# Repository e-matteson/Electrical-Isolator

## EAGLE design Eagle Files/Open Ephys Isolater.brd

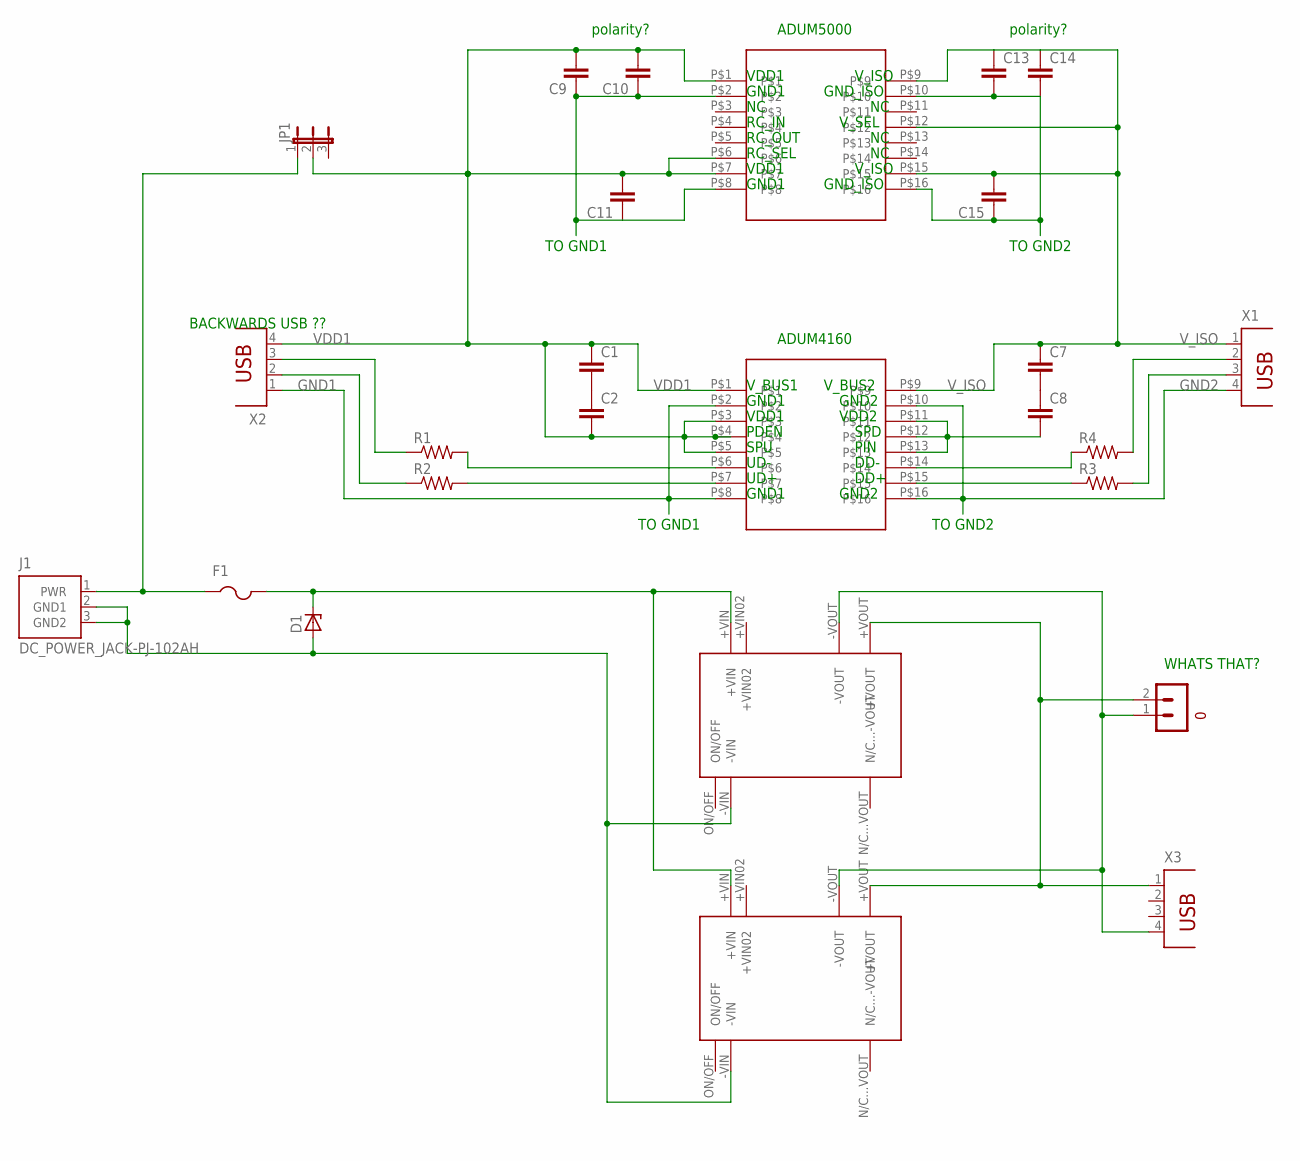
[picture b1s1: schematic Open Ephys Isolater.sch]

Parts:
C1, C2, C7, C8, C9, C10, C11, C13, C14, C15: C_0201; 0201
D1: ZENER-DIODESMB; SMB
F1: PTCFUSE-1206; R1206
J1: DC_POWER_JACK-PJ-102AH; PJ-102AH
JP1: JP2E; JP2
R1, R2, R3, R4: R-US_R2512; R2512
S1: TERMINAL_BLOCK_2-3.5MM-5V; TERMINAL_BLOCK_3.5MM_2_5V
U$1, U$2: ADUM4160
U$3, U$4: NCM6S0505EC
X1, X3: PN87520
X2: PN61729

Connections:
GND1: C9.1, C10.1, C11.1, D1.A, J1.2 (GND1), J1.3 (GND2), U$1.P$2, U$1.P$8, U$2.P$2, U$2.P$8, U$3.-VIN, U$4.-VIN, X2.1
GND2: C13.2, C14.2, C15.1, S1.1 (0), U$1.P$10, U$1.P$16, U$2.P$10, U$2.P$16, U$3.-VOUT, U$4.-VOUT, X1.4, X3.4
unnamed: R1.1, X2.3
unnamed: R1.2, U$2.P$6
unnamed: R2.2, U$2.P$7
unnamed: F1.1, J1.1 (PWR), JP1.1
unnamed: C7.2, C8.1
unnamed: R2.1, X2.2
unnamed: C8.2, U$2.P$11, U$2.P$12, U$2.P$13
unnamed: C1.2, C2.1
unnamed: S1.2 (1), U$3.+VOUT, U$4.+VOUT, X3.1
unnamed: R4.1, U$2.P$14
unnamed: R3.1, U$2.P$15
unnamed: R3.2, X1.3
unnamed: R4.2, X1.2
unnamed: D1.C, F1.2, U$3.+VIN, U$4.+VIN
VDD1: C1.1, C2.2, C9.2, C10.2, C11.2, JP1.2, U$1.P$1, U$1.P$6, U$1.P$7, U$2.P$1, U$2.P$3, U$2.P$4, U$2.P$5, X2.4
V_ISO: C7.1, C13.1, C14.1, C15.2, U$1.P$9, U$1.P$12, U$1.P$15, U$2.P$9, X1.1

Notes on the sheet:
ADUM4160
ADUM5000
polarity?
VDD1
GND1
RC_IN
RC_OUT
RC_SEL
V_ISO
GND_ISO
V_SEL
V_BUS1
PDEN
SPU
UD-
UD+
GND2
V_BUS2
VDD2
SPD
PIN
DD-
DD+
BACKWARDS USB ??
TO GND2
TO GND1
WHATS THAT?

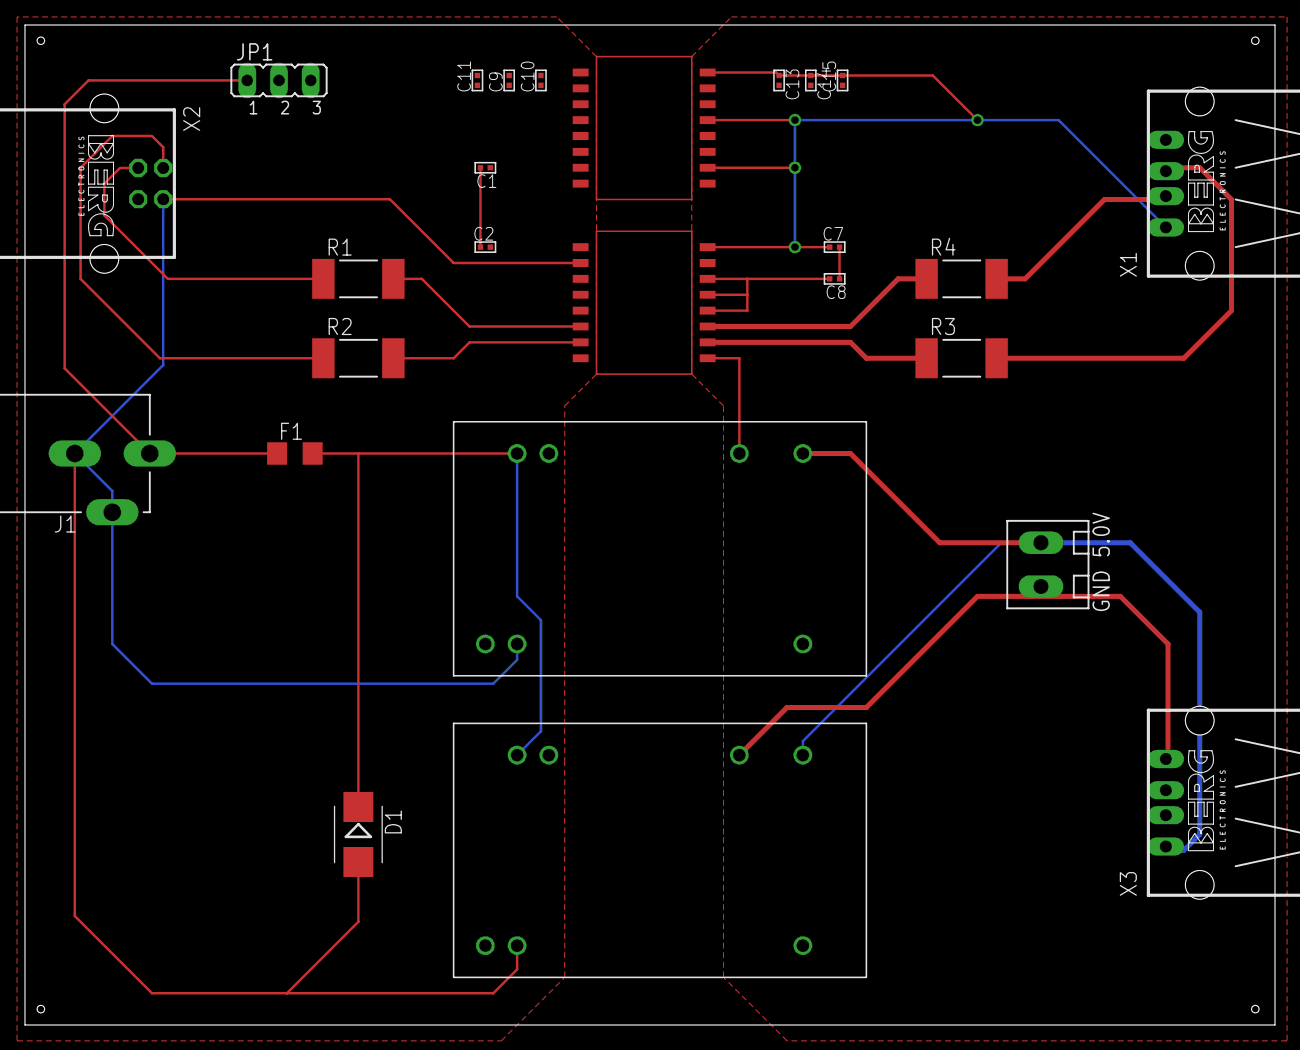
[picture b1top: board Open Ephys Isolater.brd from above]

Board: 2 copper layers, 100.0 x 80.0 mm, 26 parts (0 on the bottom side), 18 nets.

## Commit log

2015-06-26 For isolating open ephys [EEG]
2015-09-06 neatened nets on schematic
2015-09-06 more names, labels, neatening
2015-09-24 cleaned up schematic
